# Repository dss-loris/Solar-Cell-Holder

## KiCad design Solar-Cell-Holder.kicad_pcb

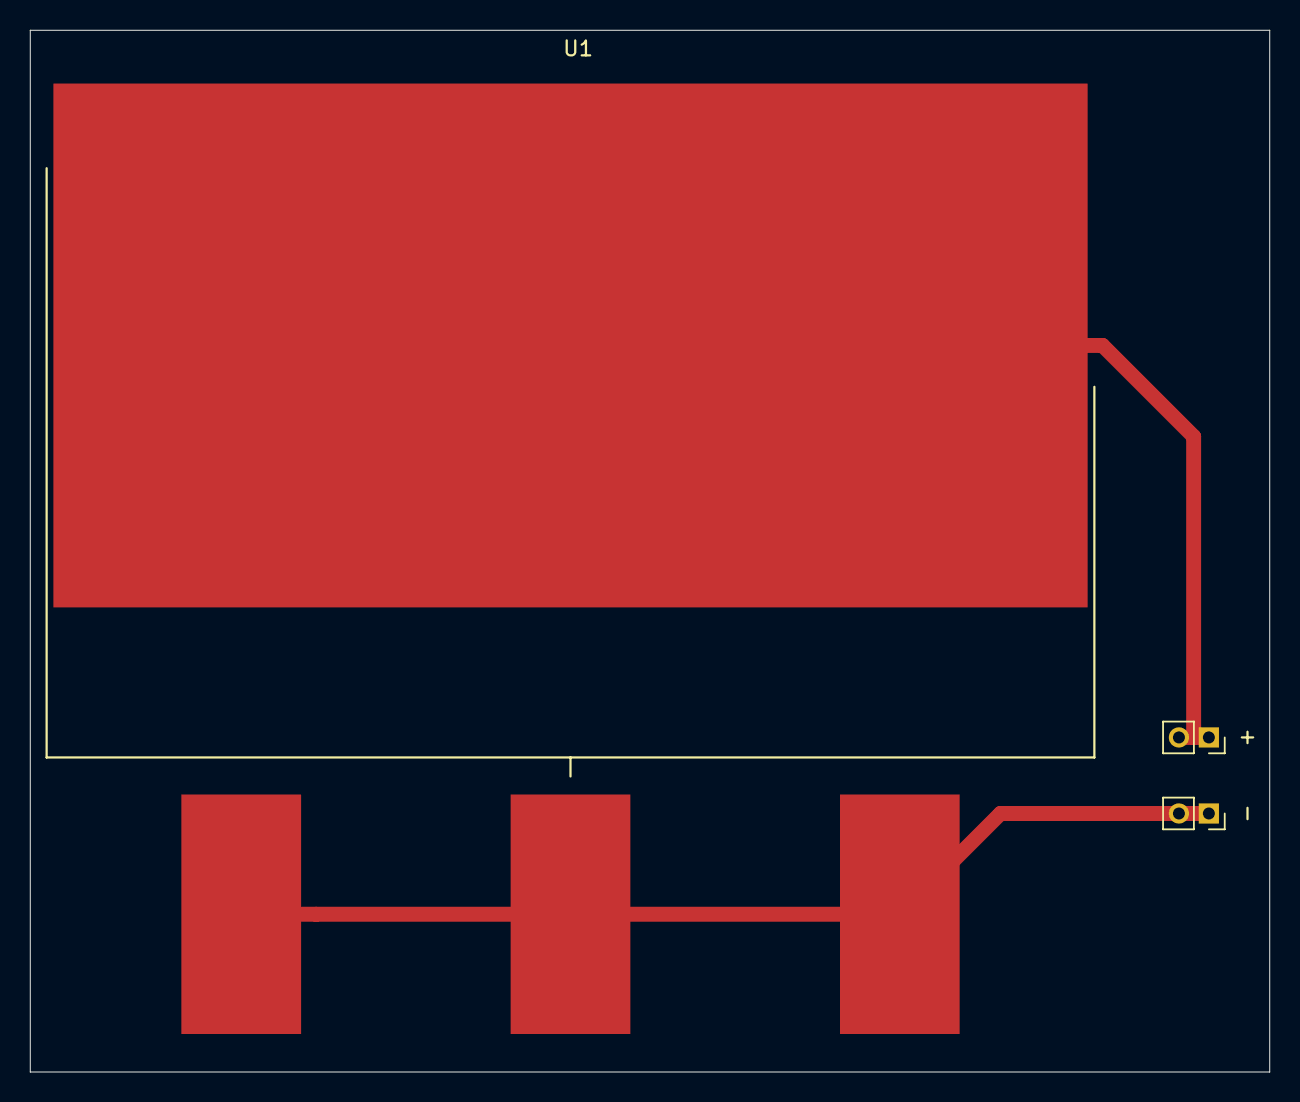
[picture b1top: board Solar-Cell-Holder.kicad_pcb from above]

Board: 2 copper layers, 82.8 x 69.6 mm, 3 parts (0 on the bottom side), 2 nets.

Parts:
+: Conn_01x02_Female; PinSocket_1x02_P2.00mm_Vertical
-: Conn_01x02_Female; PinSocket_1x02_P2.00mm_Vertical
U1: XTJ; XTJ-Triple-Junction

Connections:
unnamed: -.1, -.2, U1.1, U1.2, U1.3
unnamed: +.1, +.2, U1.4

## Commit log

2019-11-22 init
2019-11-22 finished
